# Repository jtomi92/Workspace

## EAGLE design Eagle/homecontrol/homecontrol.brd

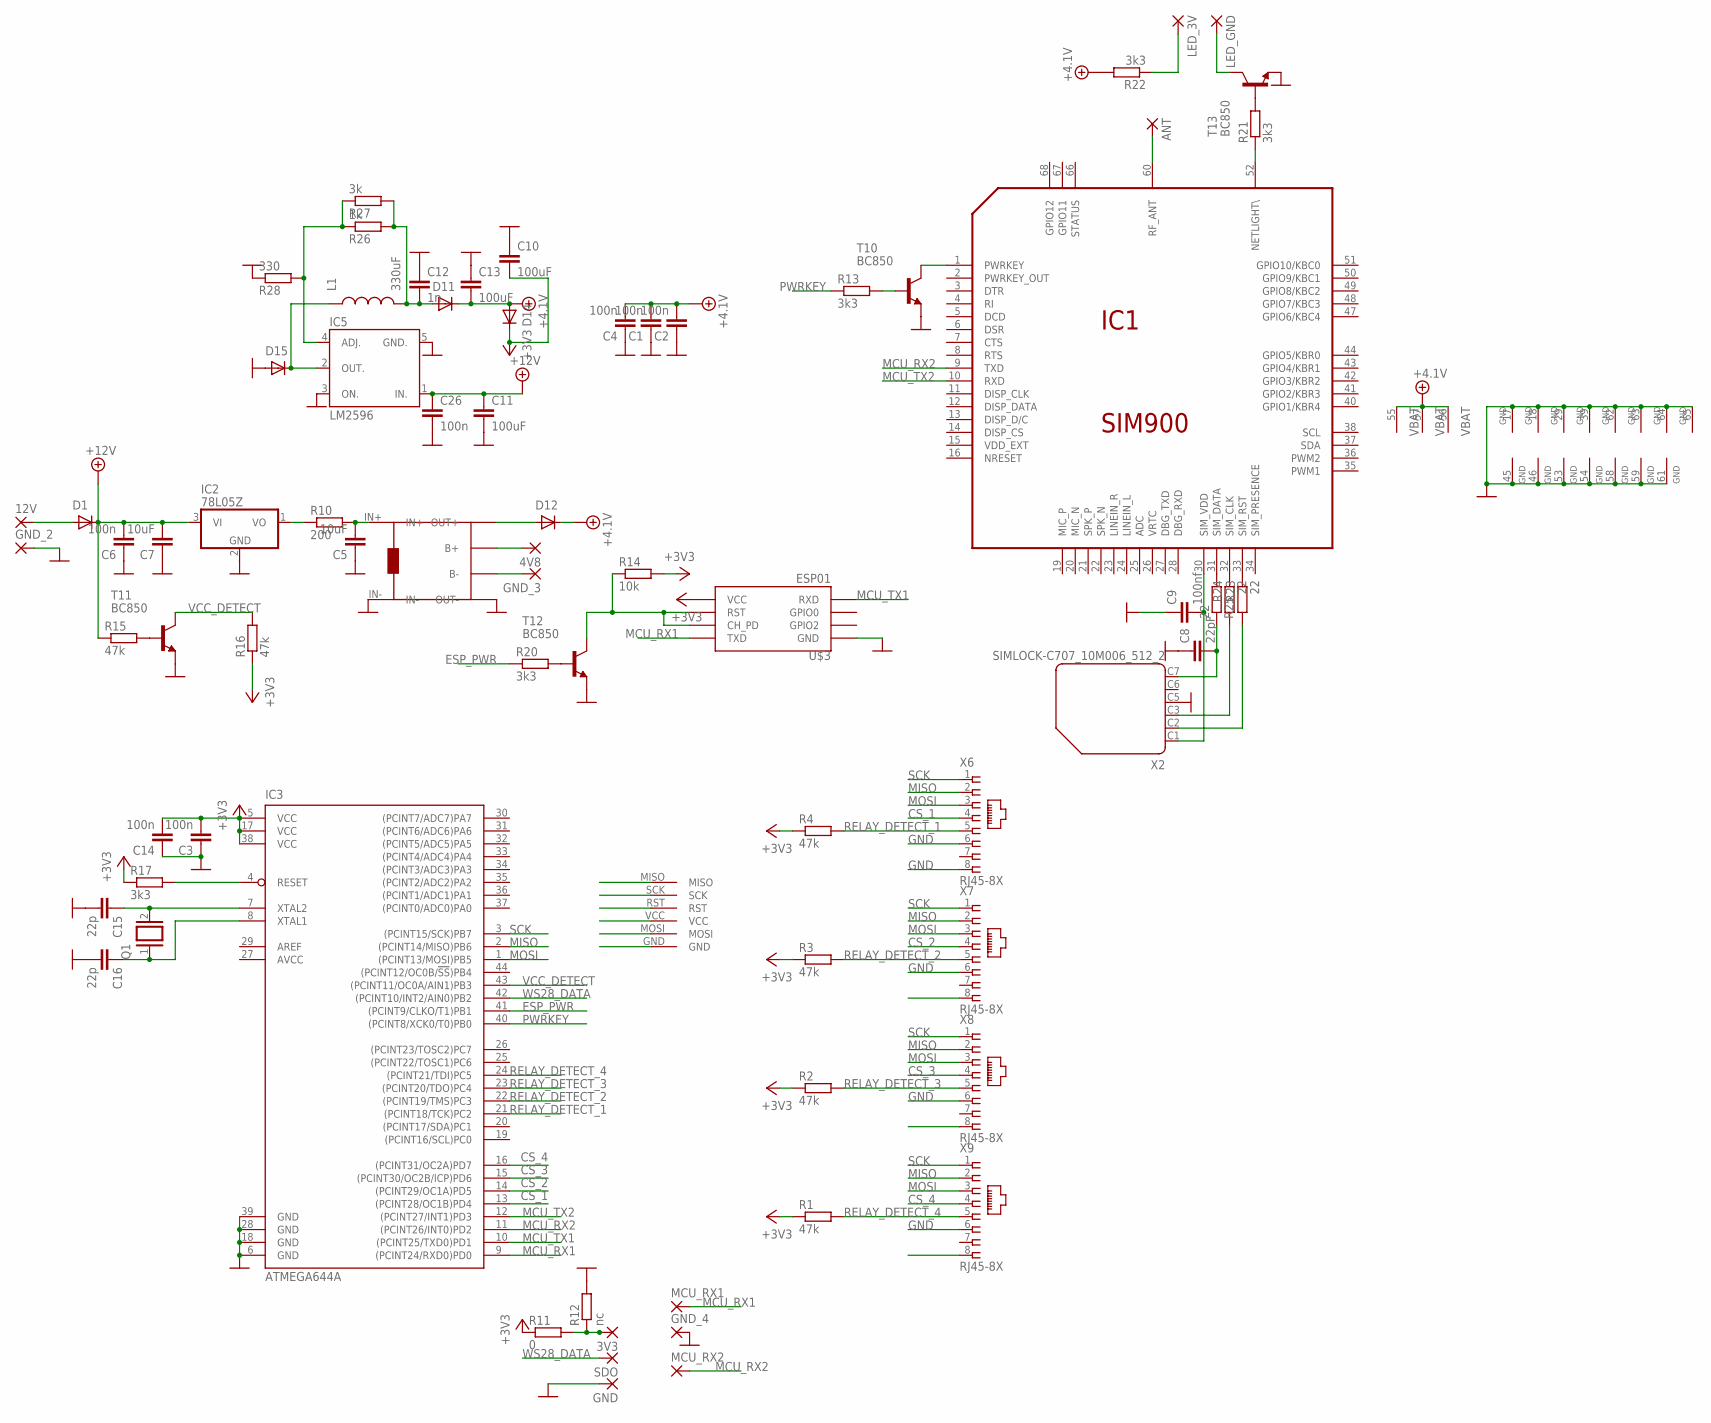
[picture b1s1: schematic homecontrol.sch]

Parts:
3V3: 2,15/1,0
4V8: WIREPAD2,15/1,0; 2,15/1,0
12V: 2,54/0,8
ANT: 2,54/0,8
C1, C2, C3, C4, C6, C14: 100n; C1206
C5, C7: 10uF; C1206
C8: 22pF; C1206K
C9: 100nf; C1206K
C10, C11: 100uF; SMD-CAP
C12: 1n; C1206K
C13: 100uF; C025-050X050
C15, C16: 22p; C1206
C26: 100n; C1206K
D1, D11, D12, D14, D15: GF1; SMA-DO214AC
GND: 2,54/0,8
GND_2, GND_3, GND_4: 2,15/1,0
IC1: SIM900
IC2: 78L05Z; TO92
IC3: ATMEGA644A; TQFP44
IC5: LM2596; TO263-5
L1: 330uF; SMD-COIL
LED_3V: WIREPAD2,15/1,0; 2,15/1,0
LED_GND: WIREPAD2,15/1,0; 2,15/1,0
MCU_RX1, MCU_RX2: 2,15/1,0
Q1: XTAL/S; QS
R1, R2, R3, R4, R15, R16: 47k; M3216
R10: 200; M3216
R11: 0; M3216
R12: nc; M3216
R13, R17, R20, R21, R22: 3k3; M3216
R14: 10k; M3216
R23, R24, R25: 22; M1206
R26: 1k; M3216
R27: 3k; M3216
R28: 330; M3216
SDO: 2,15/1,0
T10, T11, T12, T13: BC850; SOT23
U$1: AVR_ISP
U$2: AKUTOLTO
U$3: ESP01
X2: SIMLOCK-C707_10M006_512_2; C707_10M006_512_2
X6, X7, X8, X9: RJ45-8X; RJ45-NO-SHIELD

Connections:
+3V3: C3.2, C10.P$2 (2), C14.2, D14.K (C), IC3.5 (VCC), IC3.17 (VCC), IC3.38 (VCC), R1.1, R2.1, R3.1, R4.1, R11.1, R14.2, R16.1, R17.1, U$1.VCC, U$3.VCC
+4.1V: C1.2, C2.2, C4.2, C13.2, D11.K (C), D12.K (C), D14.A, IC1.55 (VBAT), IC1.56 (VBAT), IC1.57 (VBAT), R22.2
+12V: C6.2, C7.2, C11.P$1 (1), C26.1, D1.K (C), IC2.3 (VI), IC5.1 (IN.), R15.1
AVCC: IC3.27 (AVCC)
CS_1: IC3.13 ((PCINT28/OC1B)PD4), X6.4
CS_2: IC3.14 ((PCINT29/OC1A)PD5), X7.4
CS_3: IC3.15 ((PCINT30/OC2B/ICP)PD6), X8.4
CS_4: IC3.16 ((PCINT31/OC2A)PD7), X9.4
ESP_PWR: IC3.41 ((PCINT9/CLKO/T1)PB1), R20.1
GND: C1.1, C2.1, C3.1, C4.1, C5.1, C6.1, C7.1, C8.1, C9.1, C10.P$1 (1), C11.P$2 (2), C12.1, C13.1, C14.1, C15.2, C16.2, C26.2, D15.A, GND.1, GND_2.1, GND_4.1, IC1.17 (GND), IC1.18 (GND), IC1.29 (GND), IC1.39 (GND), IC1.45 (GND), IC1.46 (GND), IC1.53 (GND), IC1.54 (GND), IC1.58 (GND), IC1.59 (GND), IC1.61 (GND), IC1.62 (GND), IC1.63 (GND), IC1.64 (GND), IC1.65 (GND), IC2.2 (GND), IC3.6 (GND), IC3.18 (GND), IC3.28 (GND), IC3.39 (GND), IC5.3 (ON.), IC5.5 (GND.), R12.2, R28.1, T10.2 (E), T11.2 (E), T12.2 (E), T13.2 (E), U$1.GND, U$2.IN-, U$2.OUT-, U$3.GND, X2.C5 (4), X6.6, X6.8, X7.6, X7.8, X8.6, X8.8, X9.6, X9.8
MCU_RX1: IC3.9 ((PCINT24/RXD0)PD0), MCU_RX1.1, U$3.TX (TXD)
MCU_RX2: IC1.9 (TXD), IC3.11 ((PCINT26/INT0)PD2), MCU_RX2.1
MCU_TX1: IC3.10 ((PCINT25/TXD0)PD1), U$3.RX (RXD)
MCU_TX2: IC1.10 (RXD), IC3.12 ((PCINT27/INT1)PD3)
MISO: IC3.2 ((PCINT14/MISO)PB6), U$1.MISO, X6.2, X7.2, X8.2, X9.2
MOSI: IC3.1 ((PCINT13/MOSI)PB5), U$1.MOSI, X6.3, X7.3, X8.3, X9.3
unnamed: C12.2, D11.A, L1.P$2 (2), R26.2, R27.2
unnamed: C5.2, R10.2, U$2.IN+
unnamed: D12.A, U$2.OUT+
unnamed: IC2.1 (VO), R10.1
unnamed: 3V3.1, R11.2, R12.1
unnamed: R13.2, T10.1 (B)
unnamed: IC1.1 (PWRKEY), T10.3 (C)
unnamed: D15.K (C), IC5.2 (OUT.), L1.P$1 (1)
unnamed: 12V.1, D1.A
unnamed: R14.1, T12.3 (C), U$3.CH_PD, U$3.RST
unnamed: 4V8.1, U$2.B+
unnamed: R15.2, T11.1 (B)
unnamed: GND_3.1, U$2.B-
unnamed: C15.1, IC3.7 (XTAL2), Q1.2
unnamed: R20.2, T12.1 (B)
unnamed: IC5.4 (ADJ.), R26.1, R27.1, R28.2
unnamed: ANT.1, IC1.60 (RF_ANT)
unnamed: IC1.52 (NETLIGHT\), R21.1
unnamed: R21.2, T13.1 (B)
unnamed: LED_GND.1, T13.3 (C)
unnamed: LED_3V.1, R22.1
unnamed: C9.2, IC1.30 (SIM_VDD), X2.C1 (1)
unnamed: R23.2, X2.C2 (2)
unnamed: R24.2, X2.C3 (3)
unnamed: C8.2, R25.1, X2.C7 (6)
unnamed: IC1.33 (SIM_RST), R23.1
unnamed: IC1.32 (SIM_CLK), R24.1
unnamed: IC1.31 (SIM_DATA), R25.2
unnamed: C16.1, IC3.8 (XTAL1), Q1.1
PWRKEY: IC3.40 ((PCINT8/XCK0/T0)PB0), R13.1
RELAY_DETECT_1: IC3.21 ((PCINT18/TCK)PC2), R4.2, X6.5
RELAY_DETECT_2: IC3.22 ((PCINT19/TMS)PC3), R3.2, X7.5
RELAY_DETECT_3: IC3.23 ((PCINT20/TDO)PC4), R2.2, X8.5
RELAY_DETECT_4: IC3.24 ((PCINT21/TDI)PC5), R1.2, X9.5
RESET: IC3.4 (RESET), R17.2, U$1.RST
SCK: IC3.3 ((PCINT15/SCK)PB7), U$1.SCK, X6.1, X7.1, X8.1, X9.1
VCC_DETECT: IC3.43 ((PCINT11/OC0A/AIN1)PB3), R16.2, T11.3 (C)
WS28_DATA: IC3.42 ((PCINT10/INT2/AIN0)PB2), SDO.1

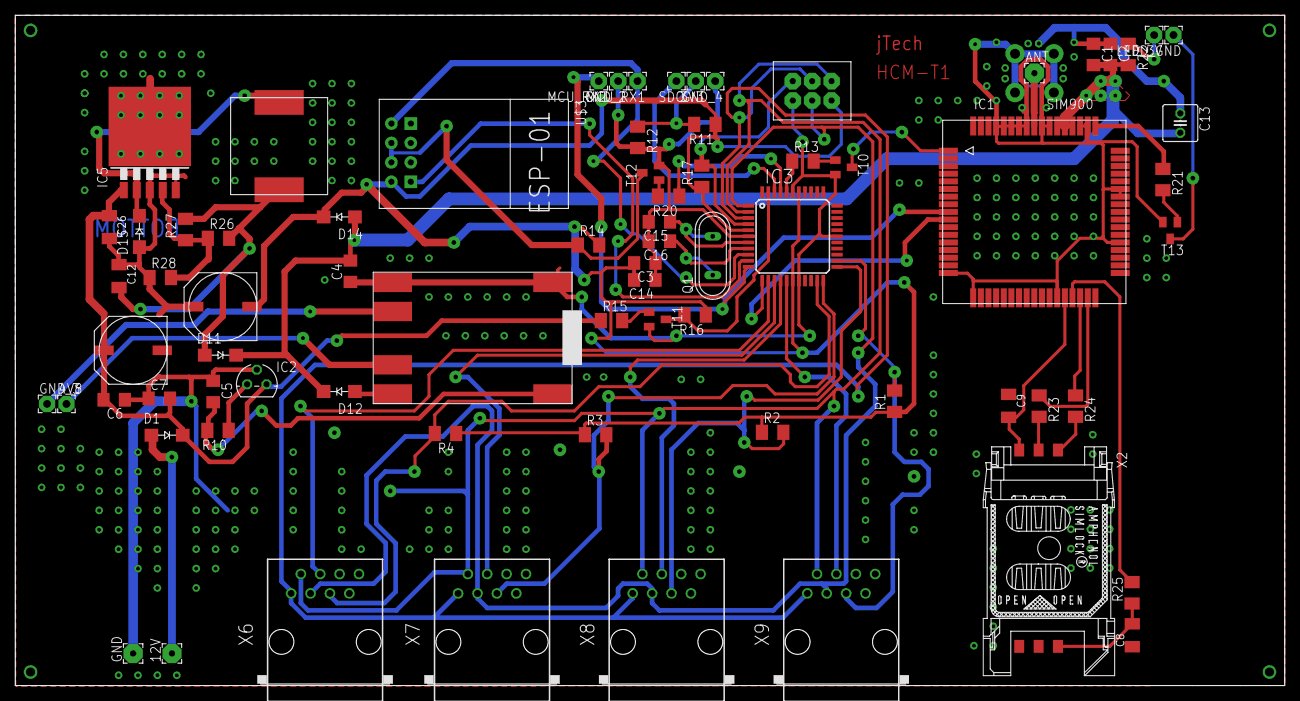
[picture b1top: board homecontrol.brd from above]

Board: 2 copper layers, 166.2 x 87.7 mm, 74 parts (0 on the bottom side), 53 nets.

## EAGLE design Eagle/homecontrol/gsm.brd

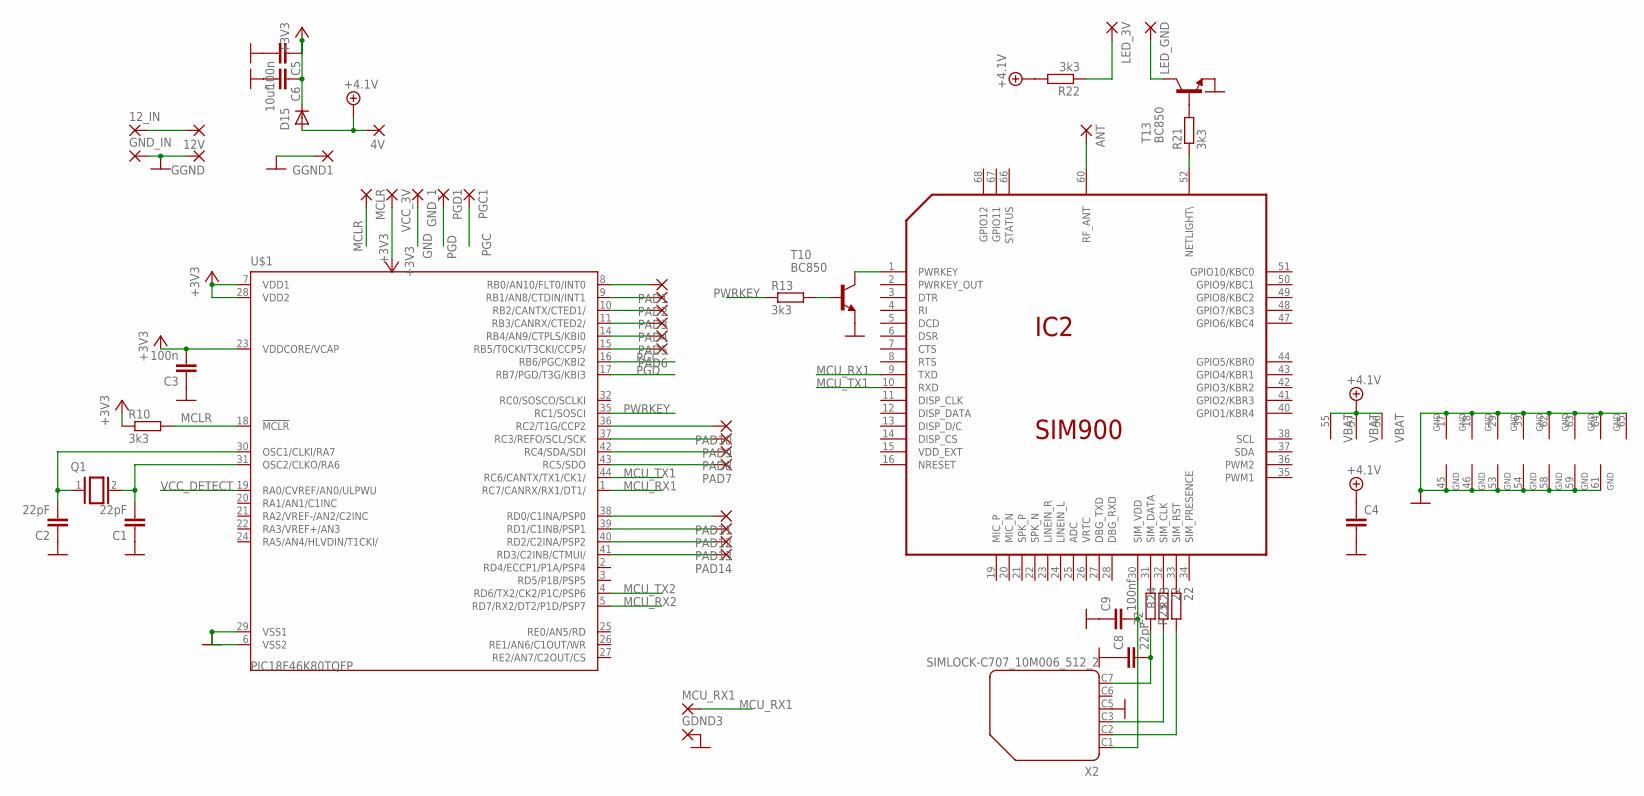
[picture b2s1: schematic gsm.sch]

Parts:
4V, 12V: SMD2; SMD1,27-2,54
12_IN: 2,15/1,0
ANT: 2,54/0,8
C1, C2: 22pF; C1206
C3, C5: 100n; C1206
C4: C-EU025-050X050; C025-050X050
C6: 10uf; C1206
C8: 22pF; C1206K
C9: 100nf; C1206K
D15: GF1; SMA-DO214AC
GDND3: 2,15/1,0
GGND, GGND1: SMD2; SMD1,27-2,54
GND_1: 2,15/1,0
GND_IN: 2,15/1,0
IC2: SIM900
LED_3V: WIREPAD2,15/1,0; 2,15/1,0
LED_GND: WIREPAD2,15/1,0; 2,15/1,0
MCLR: 2,15/1,0
MCU_RX1: 2,15/1,0
PAD1, PAD2, PAD3, PAD4, PAD5, PAD6, PAD7, PAD8, PAD9, PAD10, PAD11, PAD12, PAD13, PAD14: SMD2; SMD1,27-2,54
PGC1: 2,15/1,0
PGD1: 2,15/1,0
Q1: XTAL/S; QS
R10, R13, R21, R22: 3k3; M3216
R23, R24, R25: 22; M1206
T10, T13: BC850; SOT23
U$1: PIC18F46K80TQFP; TQFP44
VCC_3V: 2,15/1,0
X2: SIMLOCK-C707_10M006_512_2; C707_10M006_512_2

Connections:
+3V3: C3.2, C5.1, C6.1, D15.K (C), R10.1, U$1.7 (VDD1), U$1.23 (VDDCORE/VCAP), U$1.28 (VDD2), VCC_3V.1
+4.1V: 4V.1, C4.1, D15.A, IC2.55 (VBAT), IC2.56 (VBAT), IC2.57 (VBAT), R22.2
GND: C1.1, C2.1, C3.1, C4.2, C5.2, C6.2, C8.1, C9.1, GDND3.1, GGND.1, GGND1.1, GND_1.1, GND_IN.1, IC2.17 (GND), IC2.18 (GND), IC2.29 (GND), IC2.39 (GND), IC2.45 (GND), IC2.46 (GND), IC2.53 (GND), IC2.54 (GND), IC2.58 (GND), IC2.59 (GND), IC2.61 (GND), IC2.62 (GND), IC2.63 (GND), IC2.64 (GND), IC2.65 (GND), T10.2 (E), T13.2 (E), U$1.6 (VSS2), U$1.29 (VSS1), X2.C5 (4)
MCLR: MCLR.1, R10.2, U$1.18 (!MCLR)
MCU_RX1: IC2.9 (TXD), MCU_RX1.1, U$1.1 (RC7/CANRX/RX1/DT1/)
MCU_RX2: U$1.5 (RD7/RX2/DT2/P1D/PSP7)
MCU_TX1: IC2.10 (RXD), U$1.44 (RC6/CANTX/TX1/CK1/)
MCU_TX2: U$1.4 (RD6/TX2/CK2/P1C/PSP6)
unnamed: 12V.1, 12_IN.1
unnamed: PAD1.1, U$1.8 (RB0/AN10/FLT0/INT0)
unnamed: PAD2.1, U$1.9 (RB1/AN8/CTDIN/INT1)
unnamed: PAD3.1, U$1.10 (RB2/CANTX/CTED1/)
unnamed: PAD4.1, U$1.11 (RB3/CANRX/CTED2/)
unnamed: PAD5.1, U$1.14 (RB4/AN9/CTPLS/KBI0)
unnamed: PAD6.1, U$1.15 (RB5/T0CKI/T3CKI/CCP5/)
unnamed: PAD7.1, U$1.43 (RC5/SDO)
unnamed: PAD8.1, U$1.42 (RC4/SDA/SDI)
unnamed: PAD9.1, U$1.37 (RC3/REFO/SCL/SCK)
unnamed: PAD10.1, U$1.36 (RC2/T1G/CCP2)
unnamed: PAD11.1, U$1.38 (RD0/C1INA/PSP0)
unnamed: PAD12.1, U$1.39 (RD1/C1INB/PSP1)
unnamed: PAD13.1, U$1.40 (RD2/C2INA/PSP2)
unnamed: PAD14.1, U$1.41 (RD3/C2INB/CTMUI/)
unnamed: C2.2, Q1.1, U$1.30 (OSC1/CLKI/RA7)
unnamed: C1.2, Q1.2, U$1.31 (OSC2/CLKO/RA6)
unnamed: R13.2, T10.1 (B)
unnamed: IC2.1 (PWRKEY), T10.3 (C)
unnamed: ANT.1, IC2.60 (RF_ANT)
unnamed: IC2.52 (NETLIGHT\), R21.1
unnamed: R21.2, T13.1 (B)
unnamed: LED_GND.1, T13.3 (C)
unnamed: LED_3V.1, R22.1
unnamed: C9.2, IC2.30 (SIM_VDD), X2.C1 (1)
unnamed: R23.2, X2.C2 (2)
unnamed: R24.2, X2.C3 (3)
unnamed: C8.2, R25.1, X2.C7 (6)
unnamed: IC2.33 (SIM_RST), R23.1
unnamed: IC2.32 (SIM_CLK), R24.1
unnamed: IC2.31 (SIM_DATA), R25.2
PGC: PGC1.1, U$1.16 (RB6/PGC/KBI2)
PGD: PGD1.1, U$1.17 (RB7/PGD/T3G/KBI3)
PWRKEY: R13.1, U$1.35 (RC1/SOSCI)
VCC_DETECT: U$1.19 (RA0/CVREF/AN0/ULPWU)

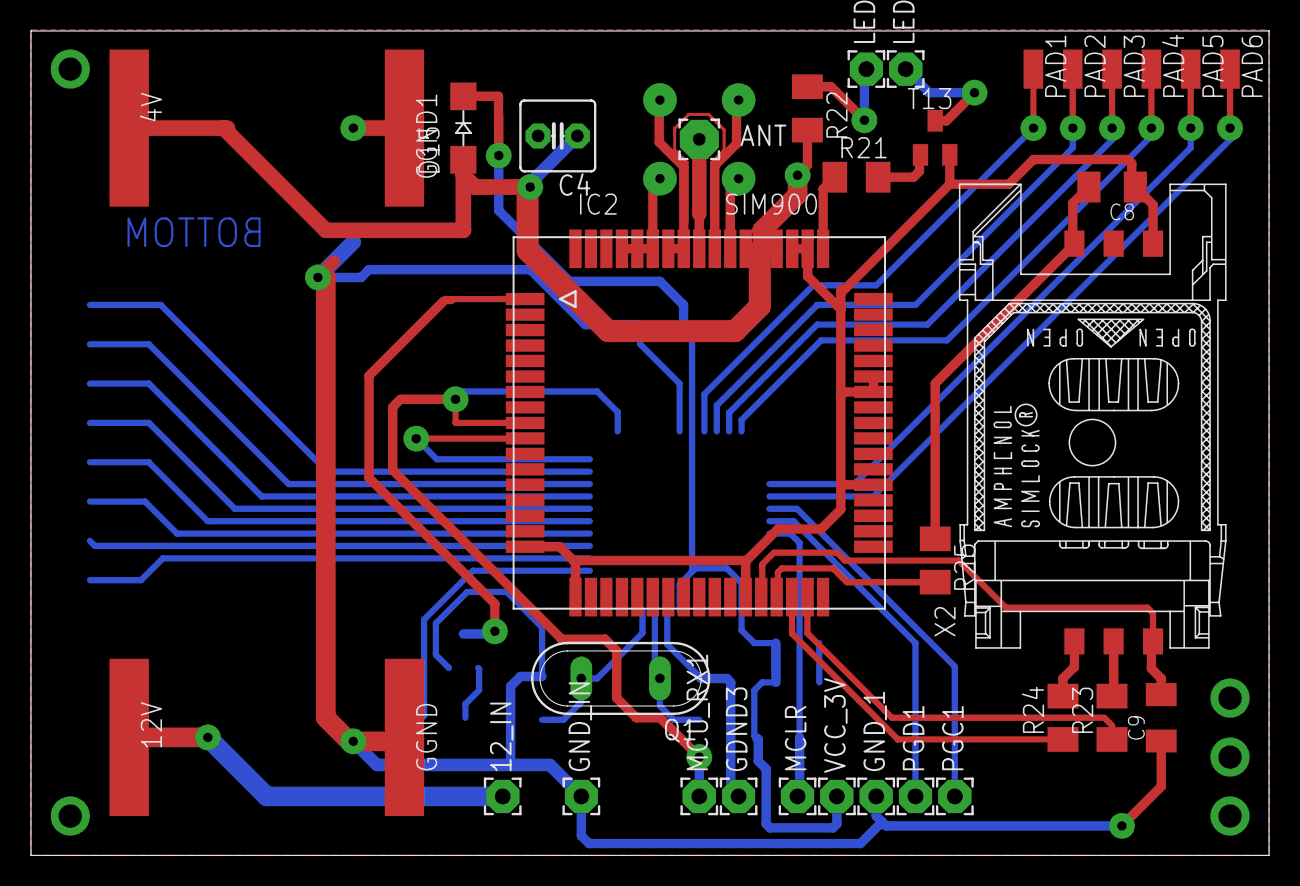
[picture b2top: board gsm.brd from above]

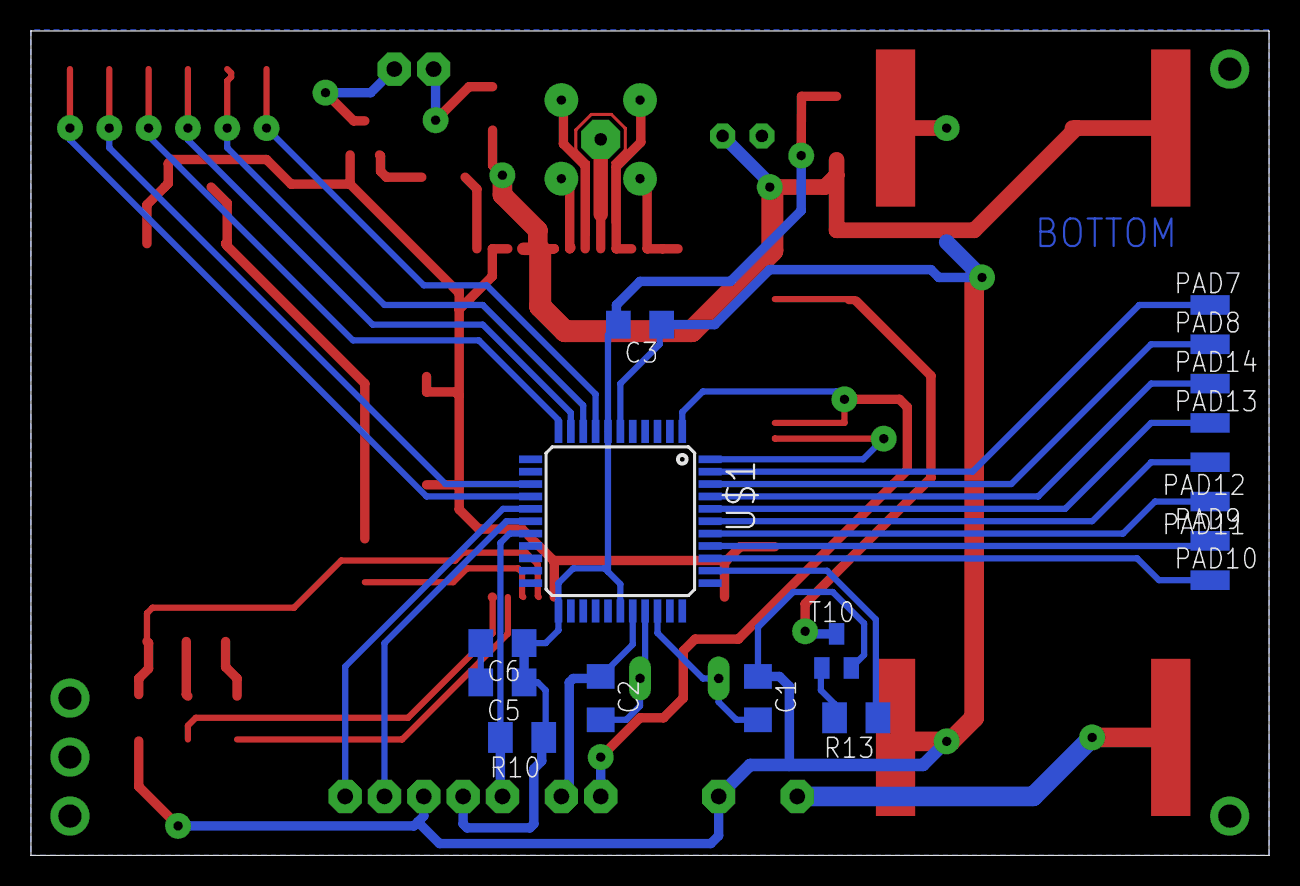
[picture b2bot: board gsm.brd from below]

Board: 2 copper layers, 80.0 x 53.3 mm, 52 parts (17 on the bottom side), 40 nets.

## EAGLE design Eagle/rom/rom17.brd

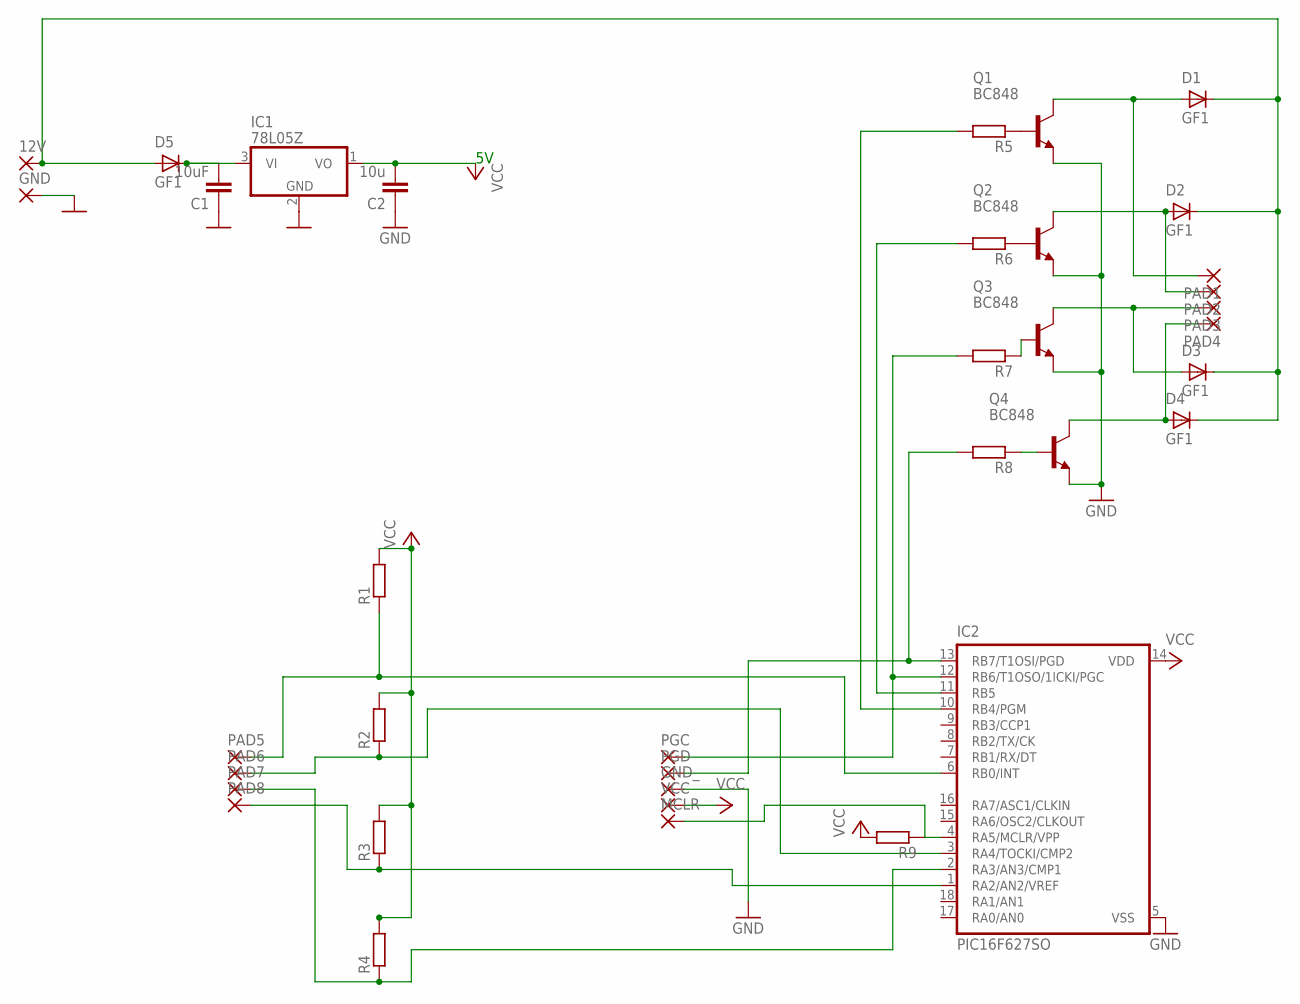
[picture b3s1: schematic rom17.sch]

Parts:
12V: 2,54/0,8
C1: 10uF; C1206
C2: 10u; C1206
D1, D2, D3, D4, D5: GF1; SMA-DO214AC
GND: 2,54/0,8
GND_: 2,15/1,0
IC1: 78L05Z; TO92
IC2: PIC16F627SO; SO-18W
MCLR: 2,15/1,0
PAD1, PAD2, PAD3, PAD4, PAD5, PAD6, PAD7, PAD8: 2,54/0,8
PGC: 2,15/1,0
PGD: 2,15/1,0
Q1, Q2, Q3, Q4: BC848; SOT23
R1, R2, R3, R4, R5, R6, R7, R8, R9: R-EU_M1206; M1206
VCC: 2,15/1,0

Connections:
unnamed: D1.A, PAD1.1, Q1.3 (C)
unnamed: D2.A, PAD2.1, Q2.3 (C)
unnamed: D3.A, PAD3.1, Q3.3 (C)
unnamed: IC2.3 (RA4/TOCKI/CMP2), PAD6.1, R2.1
unnamed: D4.A, PAD4.1, Q4.3 (C)
unnamed: Q1.1 (B), R5.1
unnamed: IC2.10 (RB4/PGM), R5.2
unnamed: IC2.11 (RB5), R6.2
unnamed: IC2.12 (RB6/T1OSO/1ICKI/PGC), PGC.1, R7.2
unnamed: IC2.2 (RA3/AN3/CMP1), PAD7.1, R4.1
unnamed: 12V.1, D1.K (C), D2.K (C), D3.K (C), D4.K (C), D5.A
unnamed: Q2.1 (B), R6.1
unnamed: Q3.1 (B), R7.1
unnamed: IC2.13 (RB7/T1OSI/PGD), PGD.1, R8.2
unnamed: Q4.1 (B), R8.1
unnamed: IC2.4 (RA5/MCLR/VPP), MCLR.1, R9.1
unnamed: C1.2, D5.K (C), IC1.3 (VI)
unnamed: C1.1, C2.1, GND.1, GND_.1, IC1.2 (GND), IC2.5 (VSS), Q1.2 (E), Q2.2 (E), Q3.2 (E), Q4.2 (E)
unnamed: IC2.1 (RA2/AN2/VREF), PAD8.1, R3.1
R5: IC2.6 (RB0/INT), PAD5.1, R1.1
VCC: C2.2, IC1.1 (VO), IC2.14 (VDD), R1.2, R2.2, R3.2, R4.2, R9.2, VCC.1

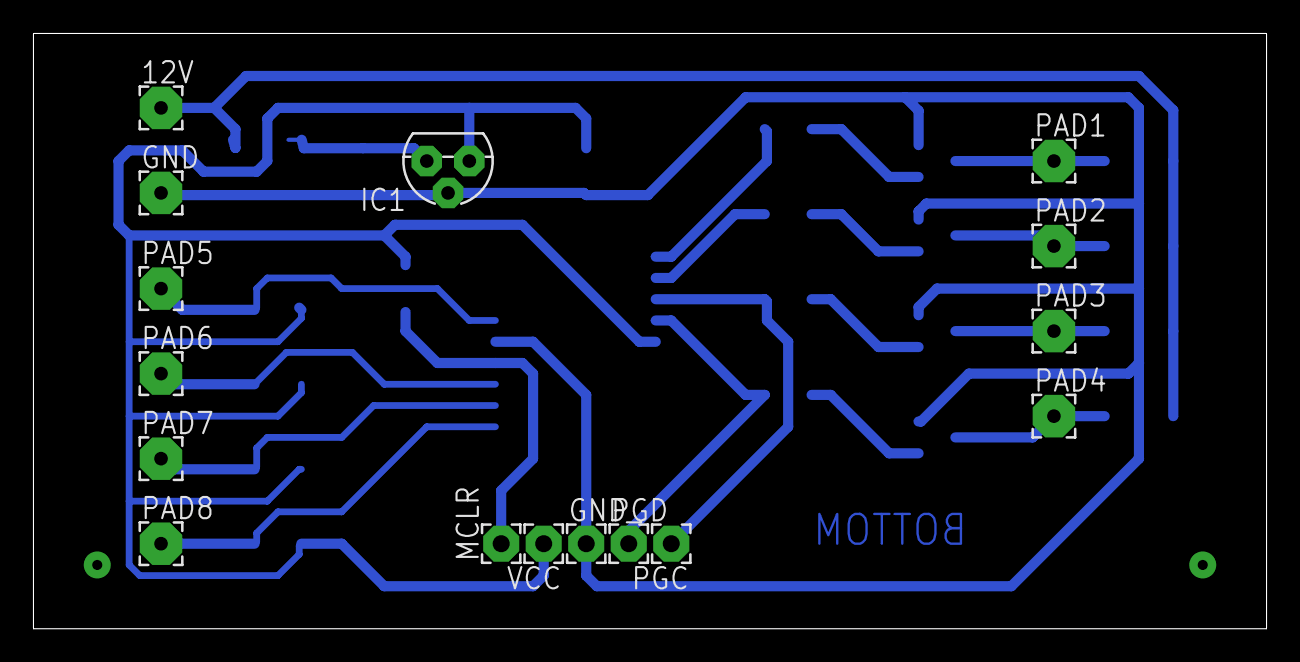
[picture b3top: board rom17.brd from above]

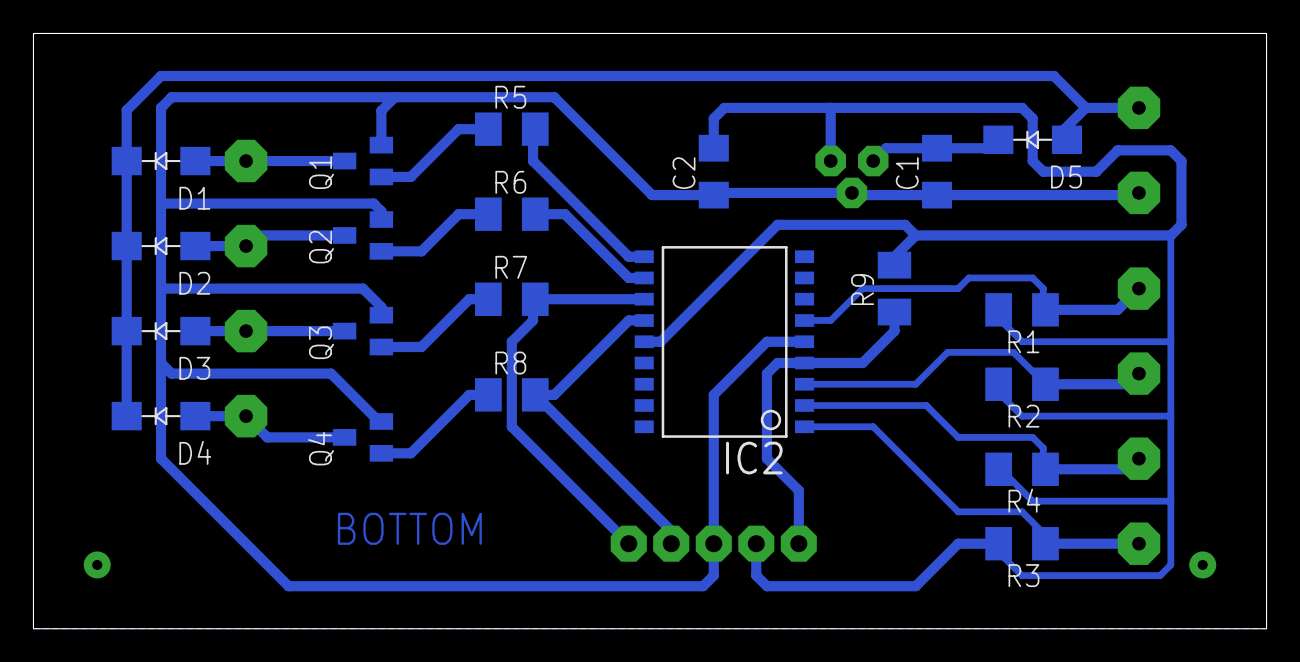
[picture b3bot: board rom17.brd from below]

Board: 2 copper layers, 73.7 x 35.6 mm, 37 parts (21 on the bottom side), 21 nets.

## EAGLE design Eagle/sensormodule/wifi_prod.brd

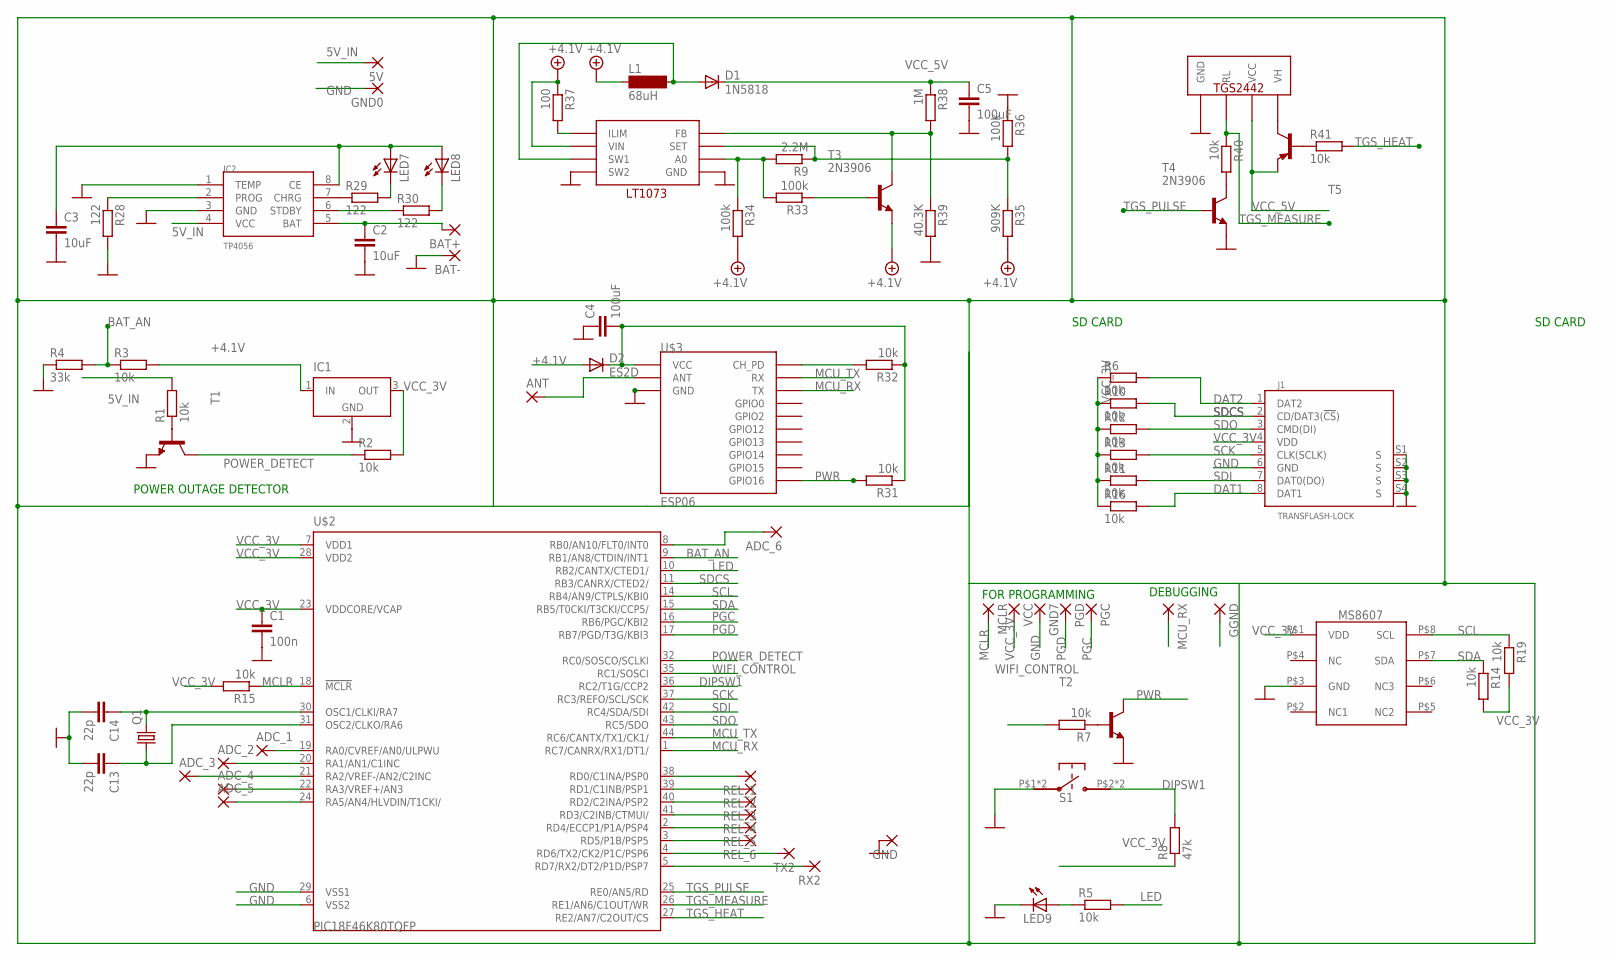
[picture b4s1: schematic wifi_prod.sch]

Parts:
5V: 2,15/1,0
ADC_1, ADC_2, ADC_3, ADC_4, ADC_5, ADC_6: 1,6/0,8
ANT: SMD2; SMD1,27-2,54
BAT+: 2,15/1,0
BAT-: 2,15/1,0
C1: 100n; C0603
C2, C3: 10uF; C1206K
C4, C5: 100uF; C1206K
C13, C14: 22p; C1206K
D1: 1N5818; SOD80C
D2: ES2D; SMB
GGND: 2,15/1,0
GND, GND0, GND7: 2,15/1,0
IC1: LT1129CST5; SOT223
IC2: TP4056; SOP-8
J1: TRANSFLASH-LOCK; TRANSFLASH-LOCK-SOCK
L1: 68uH; MS85
LED7, LED8, LED9: LG_T679-E1F1-1; PLCC2
MCLR: 2,15/1,0
MCU_RX: 2,15/1,0
PGC: 2,15/1,0
PGD: 2,15/1,0
Q1: CRYSTALHC49S; HC49/S
R1, R2, R3, R5, R6, R7, R10, R11, R12, R13, R14, R15, R16, R19, R31, R32, R40, R41: 10k; R0603
R4: 33k; R0603
R8: 47k; R0603
R9: 2.2M; R0603
R28, R29, R30: 122; R0603
R33, R34, R36: 100k; R0603
R35: 909K; R0603
R37: 100; R0603
R38: 1M; R0603
R39: 40.3K; R0603
REL_1, REL_2, REL_3, REL_4, REL_5, REL_6: 1,6/0,8
RX2: 2,15/1,0
S1: EVQP2; DIGIKEY P11084SCT-ND
T1, T2: BC849; SOT23
T3, T4: 2N3906; SOT23
T5: -PNP-SOT23-BCE; SOT23-BCE
TX2: 2,15/1,0
U$1: LT1073
U$2: PIC18F46K80TQFP; TQFP44
U$3: ESP06
U$4: TGS2442
U$6: MS8607
VCC: 2,15/1,0

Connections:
5V_IN: 5V.1, C3.1, IC2.4 (VCC), IC2.8 (CE), LED7.A, LED8.A, R1.2
+4.1V: BAT+.1, C2.1, D2.A, IC1.1 (IN), IC2.5 (BAT), L1.1, R3.2, R34.2, R35.2, R37.1, T3.2 (E), U$1.P$2 (VIN)
BAT_AN: R3.1, R4.2, U$2.9 (RB1/AN8/CTDIN/INT1)
DAT1: J1.8 (DAT1), R16.2
DAT2: J1.1 (DAT2), R6.2
DIPSW1: R8.2, S1.P$2, S1.P$4, U$2.36 (RC2/T1G/CCP2)
GND: BAT-.1, C1.2, C2.2, C3.2, C4.1, C5.2, C13.2, C14.2, GGND.1, GND.1, GND0.1, GND7.1, IC1.2 (GND), IC1.4 (GND), IC2.1 (TEMP), IC2.3 (GND), J1.6 (GND), J1.S1 (S), J1.S2 (S), J1.S3 (S), J1.S4 (S), LED9.C, R4.1, R28.2, R36.1, R39.2, S1.P$1, S1.P$3, T1.2 (E), T2.2 (E), T4.2 (E), U$1.P$4 (SW2), U$1.P$5 (GND), U$2.6 (VSS2), U$2.29 (VSS1), U$3.GND, U$3.GND1 (GND2), U$3.GND2 (GND3), U$3.GND3 (GND4), U$3.GND4 (GND5), U$3.GND5 (GND6), U$3.GND6 (GND7), U$3.GND7 (GND8), U$4.P$1 (GND), U$6.P$3 (GND)
LED: R5.2, U$2.10 (RB2/CANTX/CTED1/)
MCLR: MCLR.1, R15.1, U$2.18 (!MCLR)
MCU_RX: MCU_RX.1, U$2.1 (RC7/CANRX/RX1/DT1/), U$3.TX
MCU_TX: U$2.44 (RC6/CANTX/TX1/CK1/), U$3.RX
unnamed: C4.2, D2.C, R31.1, R32.1, U$3.VCC
unnamed: ADC_1.1, U$2.19 (RA0/CVREF/AN0/ULPWU)
unnamed: R1.1, T1.1 (B)
unnamed: ADC_2.1, U$2.20 (RA1/AN1/C1INC)
unnamed: ADC_3.1, U$2.21 (RA2/VREF-/AN2/C2INC)
unnamed: R7.1, T2.1 (B)
unnamed: ADC_4.1, U$2.22 (RA3/VREF+/AN3)
unnamed: ADC_6.1, U$2.8 (RB0/AN10/FLT0/INT0)
unnamed: LED9.A, R5.1
unnamed: REL_1.1, U$2.38 (RD0/C1INA/PSP0)
unnamed: ADC_5.1, U$2.24 (RA5/AN4/HLVDIN/T1CKI/)
unnamed: C13.1, Q1.1, U$2.31 (OSC2/CLKO/RA6)
unnamed: TX2.1, U$2.4 (RD6/TX2/CK2/P1C/PSP6)
unnamed: C14.1, Q1.2, U$2.30 (OSC1/CLKI/RA7)
unnamed: REL_2.1, U$2.39 (RD1/C1INB/PSP1)
unnamed: REL_3.1, U$2.40 (RD2/C2INA/PSP2)
unnamed: REL_4.1, U$2.41 (RD3/C2INB/CTMUI/)
unnamed: REL_5.1, U$2.2 (RD4/ECCP1/P1A/PSP4)
unnamed: REL_6.1, U$2.3 (RD5/P1B/PSP5)
unnamed: R9.2, R33.2, R34.1, U$1.P$6 (A0)
unnamed: RX2.1, U$2.5 (RD7/RX2/DT2/P1D/PSP7)
unnamed: ANT.1, U$3.ANT
unnamed: IC2.2 (PROG), R28.1
unnamed: IC2.7 (CHRG), R29.1
unnamed: IC2.6 (STDBY), R30.1
unnamed: LED7.C, R29.2
unnamed: LED8.C, R30.2
unnamed: R32.2, U$3.CH_PD
unnamed: R9.1, R35.1, R36.2, U$1.P$7 (SET)
unnamed: R33.1, T3.1 (B)
unnamed: R38.2, R39.1, T3.3 (C), U$1.P$8 (FB)
unnamed: T5.C, U$4.P$4 (VH)
unnamed: R37.2, U$1.P$1 (ILIM)
unnamed: R40.2, T4.3 (C)
unnamed: D1.A, L1.2, U$1.P$3 (SW1)
unnamed: R41.1, T5.B
PGC: PGC.1, U$2.16 (RB6/PGC/KBI2)
PGD: PGD.1, U$2.17 (RB7/PGD/T3G/KBI3)
POWER_DETECT: R2.1, T1.3 (C), U$2.32 (RC0/SOSCO/SCLKI)
PWR: R31.2, T2.3 (C), U$3.GPIO16
SCK: J1.5 (CLK(SCLK)), R13.2, U$2.37 (RC3/REFO/SCL/SCK)
SCL: R19.1, U$2.14 (RB4/AN9/CTPLS/KBI0), U$6.P$8 (SCL)
SDA: R14.1, U$2.15 (RB5/T0CKI/T3CKI/CCP5/), U$6.P$7 (SDA)
SDCS: J1.2 (CD/DAT3(!CS!)), R10.2, U$2.11 (RB3/CANRX/CTED2/)
SDI: J1.7 (DAT0(DO)), R11.2, U$2.42 (RC4/SDA/SDI)
SDO: J1.3 (CMD(DI)), R12.2, U$2.43 (RC5/SDO)
TGS_HEAT: R41.2, U$2.27 (RE2/AN7/C2OUT/CS)
TGS_MEASURE: R40.1, U$2.26 (RE1/AN6/C1OUT/WR), U$4.P$2 (RL)
TGS_PULSE: T4.1 (B), U$2.25 (RE0/AN5/RD)
VCC_3V: C1.1, IC1.3 (OUT), J1.4 (VDD), R2.2, R6.1, R8.1, R10.1, R11.1, R12.1, R13.1, R14.2, R15.2, R16.1, R19.2, U$2.7 (VDD1), U$2.23 (VDDCORE/VCAP), U$2.28 (VDD2), U$6.P$1 (VDD), VCC.1
VCC_5V: C5.1, D1.C, R38.1, T5.E, U$4.P$3 (VCC)
WIFI_CONTROL: R7.2, U$2.35 (RC1/SOSCI)

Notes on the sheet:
FOR PROGRAMMING
POWER OUTAGE DETECTOR
SD CARD
DEBUGGING

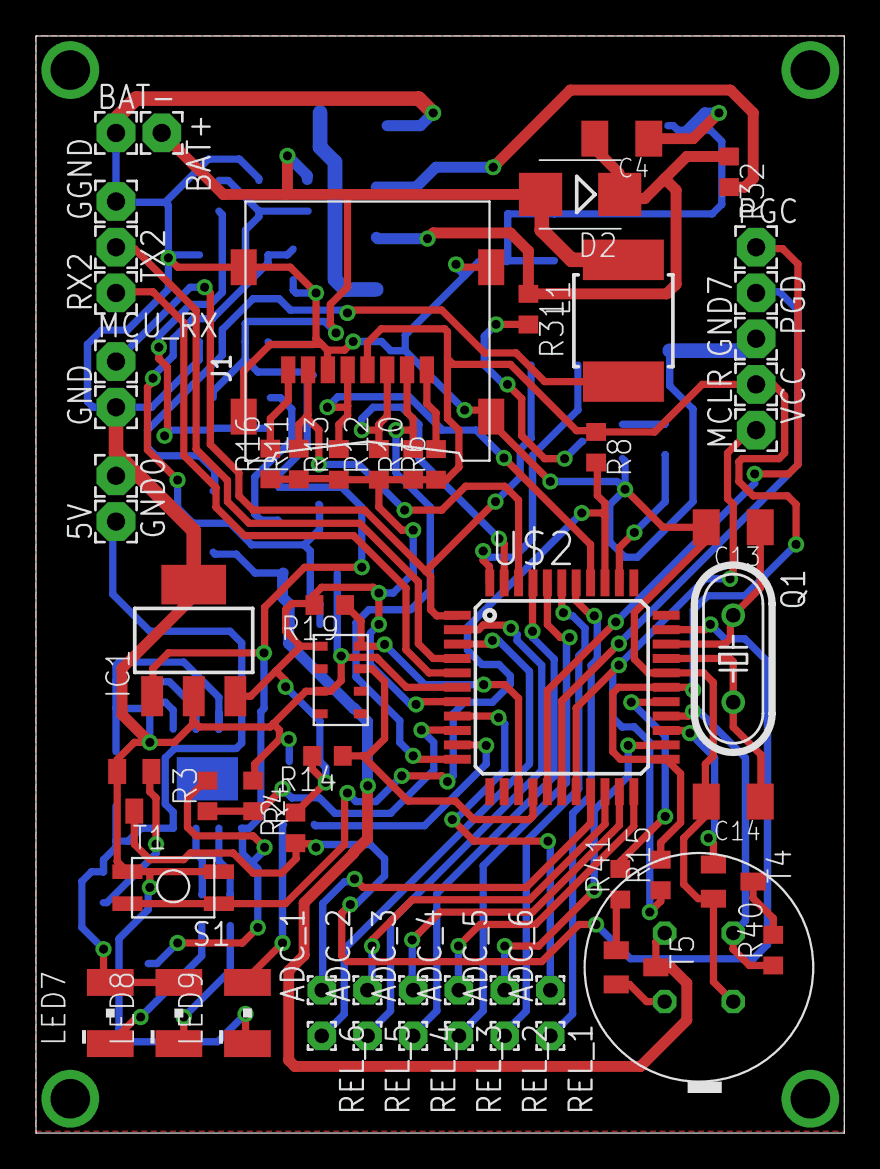
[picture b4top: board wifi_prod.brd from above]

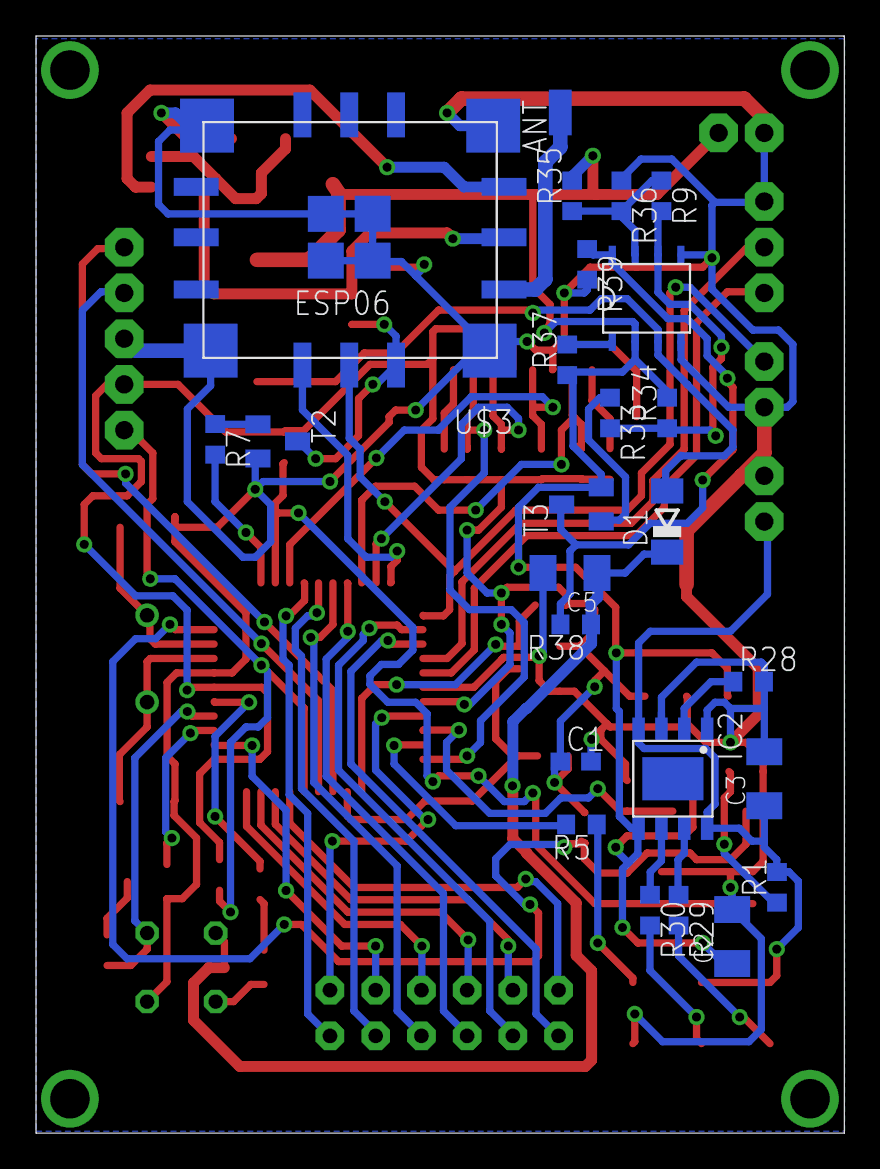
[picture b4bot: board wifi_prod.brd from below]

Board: 2 copper layers, 44.9 x 60.9 mm, 86 parts (25 on the bottom side), 63 nets.
